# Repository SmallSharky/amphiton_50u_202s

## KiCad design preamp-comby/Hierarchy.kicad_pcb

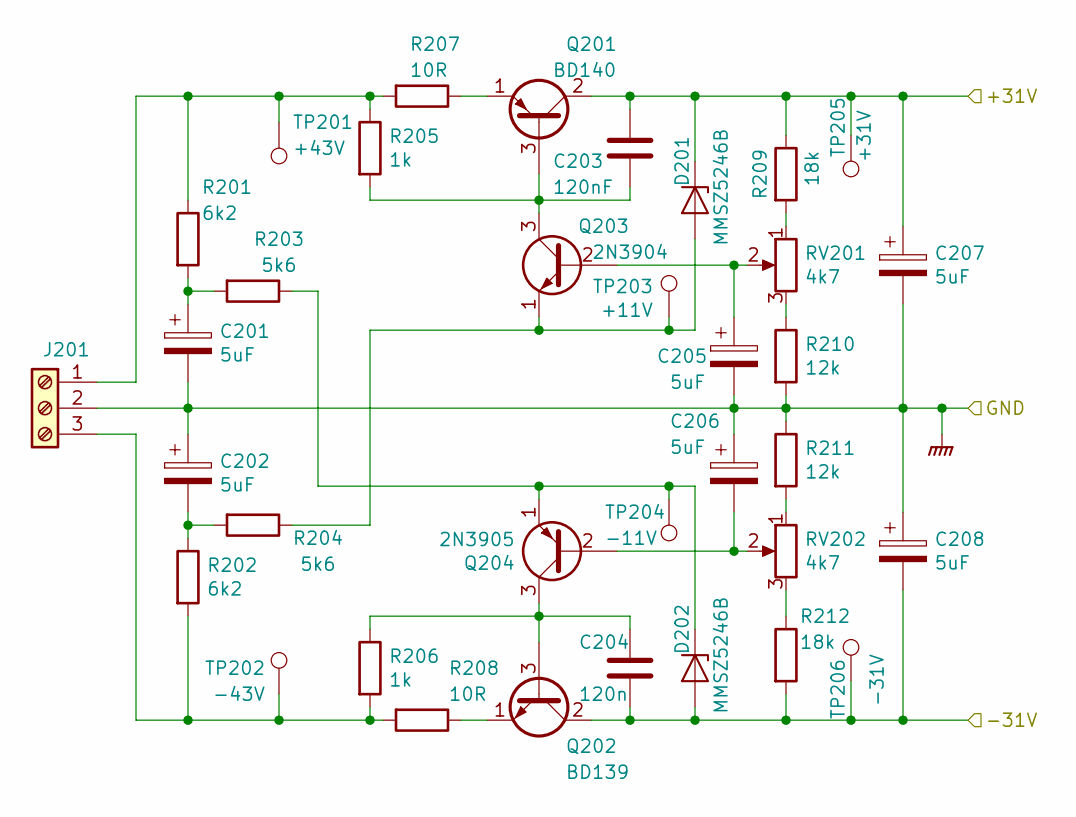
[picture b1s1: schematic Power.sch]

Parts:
C201, C202, C205, C206, C207, C208: 5uF; CP_Radial_D5.0mm_P2.00mm
C203: 120nF; C_Rect_L7.2mm_W3.0mm_P5.00mm_FKS2_FKP2_MKS2_MKP2
C204: 120n; C_Rect_L7.2mm_W3.0mm_P5.00mm_FKS2_FKP2_MKS2_MKP2
D201, D202: MMSZ5246B; D_SOD-123
J201: Screw_Terminal_01x03; TerminalBlock_MetzConnect_Type086_RT03403HBLC_1x03_P3.81mm_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
Q201: BD140; TO-126-3_Vertical
Q202: BD139; TO-126-3_Vertical
Q203: 2N3904; TO-92_Inline
Q204: 2N3905; TO-92_Inline
R201, R202: 6k2; R_1206_3216Metric_Pad1.42x1.75mm_HandSolder
R203, R204: 5k6; R_1206_3216Metric_Pad1.42x1.75mm_HandSolder
R205, R206: 1k; R_1206_3216Metric_Pad1.42x1.75mm_HandSolder
R207, R208: 10R; R_1206_3216Metric_Pad1.42x1.75mm_HandSolder
R209, R212: 18k; R_1206_3216Metric_Pad1.42x1.75mm_HandSolder
R210, R211: 12k; R_1206_3216Metric_Pad1.42x1.75mm_HandSolder
RV201, RV202: 4k7; Potentiometer_Bourns_3296W_Vertical
TP201: +43V; TestPoint_Pad_D1.5mm
TP202: -43V; TestPoint_Pad_D1.5mm
TP203: +11V; TestPoint_Pad_D1.5mm
TP204: -11V; TestPoint_Pad_D1.5mm
TP205: +31V; TestPoint_Pad_D1.5mm
TP206: -31V; TestPoint_Pad_D1.5mm

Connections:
/Power/+31V: C203.1, C207.1, D201.1 (K), Q201.2 (C), R209.1, TP205.1; also elsewhere on the board
/Power/-31V: C204.2, C208.2, D202.2 (A), Q202.2 (C), R212.2, TP206.1; also elsewhere on the board
GNDA: C201.2, C202.1, C205.2, C206.1, C207.2, C208.1, J201.2, R210.2, R211.1; also elsewhere on the board
unnamed: C201.1, R201.2, R203.2
unnamed: C202.2, R202.1, R204.2
unnamed: C203.2, Q201.3 (B), Q203.3 (C), R205.2
unnamed: C204.1, Q202.3 (B), Q204.3 (C), R206.1
unnamed: C205.1, Q203.2 (B), RV201.2
unnamed: C206.2, Q204.2 (B), RV202.2
unnamed: D201.2 (A), Q203.1 (E), R204.1, TP203.1
unnamed: D202.1 (K), Q204.1 (E), R203.1, TP204.1
unnamed: J201.1, R201.1, R205.1, R207.2, TP201.1
unnamed: J201.3, R202.2, R206.2, R208.2, TP202.1
unnamed: Q201.1 (E), R207.1
unnamed: Q202.1 (E), R208.1
unnamed: R209.2, RV201.1
unnamed: R210.1, RV201.3
unnamed: R211.2, RV202.1
unnamed: R212.1, RV202.3

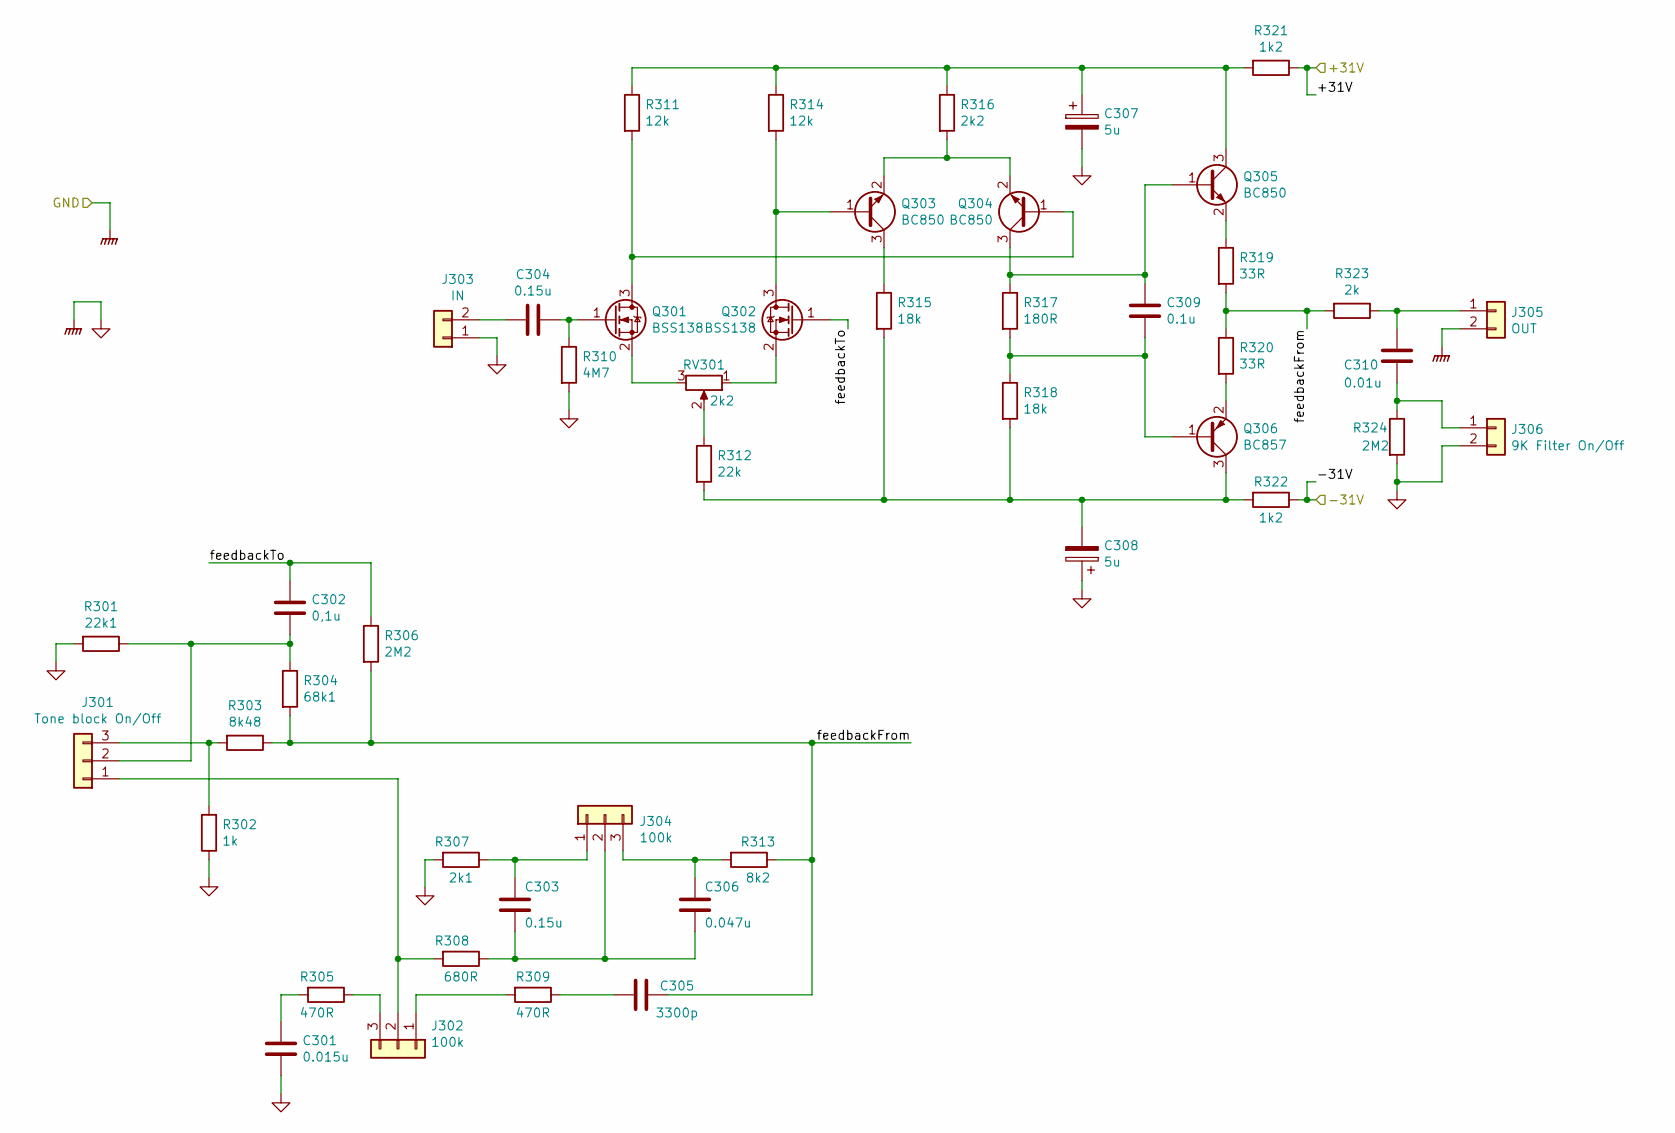
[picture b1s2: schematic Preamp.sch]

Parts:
C301: 0.015u; C_Rect_L7.2mm_W3.0mm_P5.00mm_FKS2_FKP2_MKS2_MKP2
C302: 0,1u; C_Rect_L7.2mm_W3.0mm_P5.00mm_FKS2_FKP2_MKS2_MKP2
C303, C304: 0.15u; C_Rect_L7.2mm_W3.0mm_P5.00mm_FKS2_FKP2_MKS2_MKP2
C305: 3300p; C_Rect_L7.2mm_W3.0mm_P5.00mm_FKS2_FKP2_MKS2_MKP2
C306: 0.047u; C_Rect_L7.2mm_W3.0mm_P5.00mm_FKS2_FKP2_MKS2_MKP2
C307, C308: 5u; CP_Radial_D5.0mm_P2.00mm
C309: 0.1u; C_Rect_L7.2mm_W3.0mm_P5.00mm_FKS2_FKP2_MKS2_MKP2
C310: 0.01u; C_Rect_L7.2mm_W3.0mm_P5.00mm_FKS2_FKP2_MKS2_MKP2
J301: Tone block On/Off; PinHeader_1x03_P2.54mm_Vertical
J302, J304: 100k; PinHeader_1x03_P2.54mm_Vertical
J303: IN; PinHeader_1x02_P2.54mm_Vertical
J305: OUT; PinHeader_1x02_P2.54mm_Vertical
J306: 9K Filter On/Off; PinHeader_1x02_P2.54mm_Vertical
Q301, Q302: BSS138; SOT-23
Q303, Q304, Q305: BC850; SOT-23
Q306: BC857; SOT-23
R301: 22k1; R_1206_3216Metric_Pad1.42x1.75mm_HandSolder
R302: 1k; R_1206_3216Metric_Pad1.42x1.75mm_HandSolder
R303: 8k48; R_1206_3216Metric_Pad1.42x1.75mm_HandSolder
R304: 68k1; R_1206_3216Metric_Pad1.42x1.75mm_HandSolder
R305, R309: 470R; R_1206_3216Metric_Pad1.42x1.75mm_HandSolder
R306, R324: 2M2; R_1206_3216Metric_Pad1.42x1.75mm_HandSolder
R307: 2k1; R_1206_3216Metric_Pad1.42x1.75mm_HandSolder
R308: 680R; R_1206_3216Metric_Pad1.42x1.75mm_HandSolder
R310: 4M7; R_1206_3216Metric_Pad1.42x1.75mm_HandSolder
R311, R314: 12k; R_1206_3216Metric_Pad1.42x1.75mm_HandSolder
R312: 22k; R_1206_3216Metric_Pad1.42x1.75mm_HandSolder
R313: 8k2; R_1206_3216Metric_Pad1.42x1.75mm_HandSolder
R315, R318: 18k; R_1206_3216Metric_Pad1.42x1.75mm_HandSolder
R316: 2k2; R_1206_3216Metric_Pad1.42x1.75mm_HandSolder
R317: 180R; R_1206_3216Metric_Pad1.42x1.75mm_HandSolder
R319, R320: 33R; R_1206_3216Metric_Pad1.42x1.75mm_HandSolder
R321, R322: 1k2; R_1206_3216Metric_Pad1.42x1.75mm_HandSolder
R323: 2k; R_1206_3216Metric_Pad1.42x1.75mm_HandSolder
RV301: 2k2; Potentiometer_Bourns_3296W_Vertical

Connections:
/Power/+31V: R321.1; also elsewhere on the board
/Power/-31V: R322.1; also elsewhere on the board
/Preamp/feedbackFrom: C305.1, R303.1, R304.2, R306.2, R313.1, R319.2, R320.1, R323.2
/Preamp/feedbackTo: C302.1, Q302.1 (G), R306.1
GNDA: C301.2, C307.2, C308.1, J303.1, J305.2, J306.2, R301.2, R302.1, R307.2, R310.2, R324.2; also elsewhere on the board
unnamed: C301.1, R305.2
unnamed: C302.2, J301.2, R301.1, R304.1
unnamed: C303.1, J304.1, R307.1
unnamed: C303.2, C306.2, J304.2, R308.1
unnamed: C304.1, Q301.1 (G), R310.1
unnamed: C304.2, J303.2
unnamed: C305.2, R309.1
unnamed: C306.1, J304.3, R313.2
unnamed: C307.1, Q305.3 (C), R311.1, R314.1, R316.1, R321.2
unnamed: C308.2, Q306.3 (C), R312.2, R315.2, R318.2, R322.2
unnamed: C309.1, Q304.3 (C), Q305.1 (B), R317.1
unnamed: C309.2, Q306.1 (B), R317.2, R318.1
unnamed: C310.1, J306.1, R324.1
unnamed: C310.2, J305.1, R323.1
unnamed: J301.1, J302.2, R308.2
unnamed: J301.3, R302.2, R303.2
unnamed: J302.1, R309.2
unnamed: J302.3, R305.1
unnamed: Q301.2 (S), RV301.3
unnamed: Q301.3 (D), Q304.1 (B), R311.2
unnamed: Q302.2 (S), RV301.1
unnamed: Q302.3 (D), Q303.1 (B), R314.2
unnamed: Q303.2 (E), Q304.2 (E), R316.2
unnamed: Q303.3 (C), R315.1
unnamed: Q305.2 (E), R319.1
unnamed: Q306.2 (E), R320.2
unnamed: R312.1, RV301.2

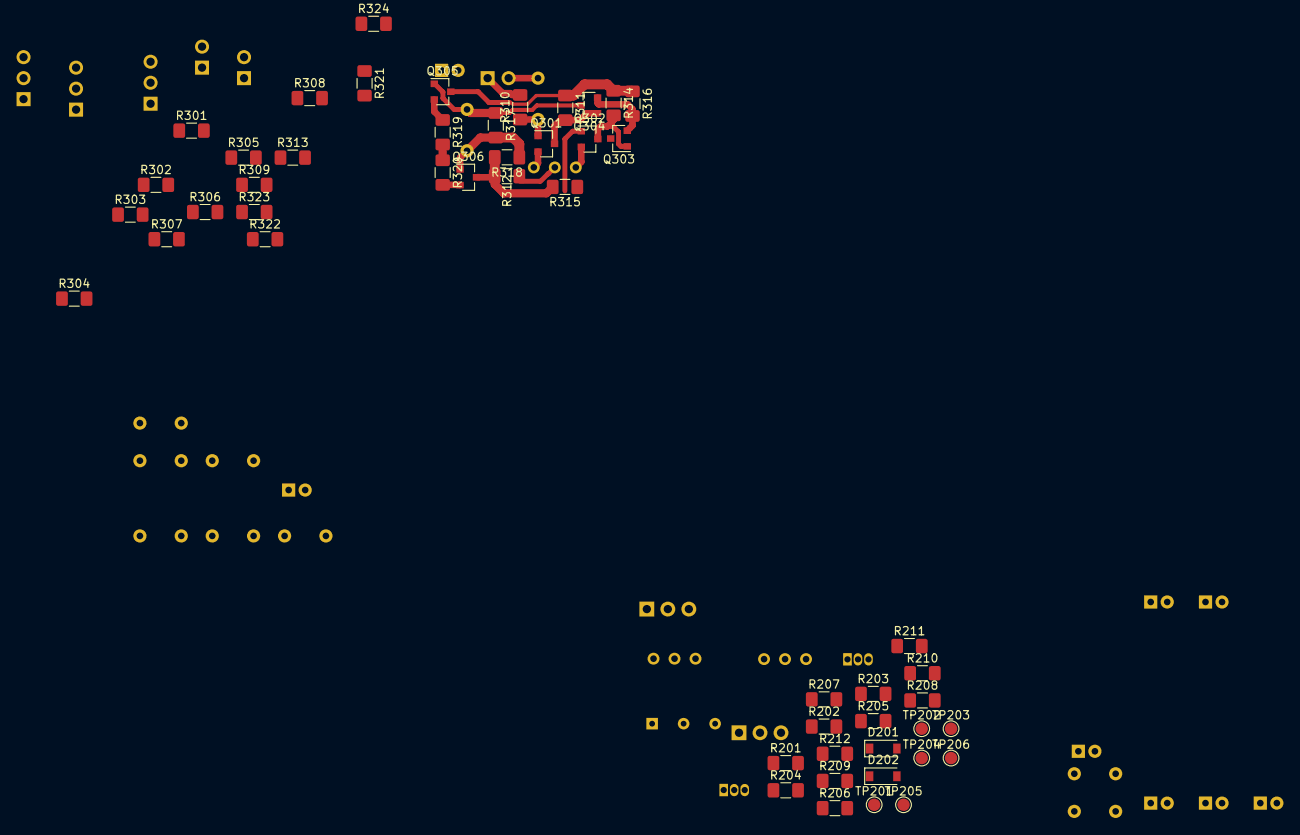
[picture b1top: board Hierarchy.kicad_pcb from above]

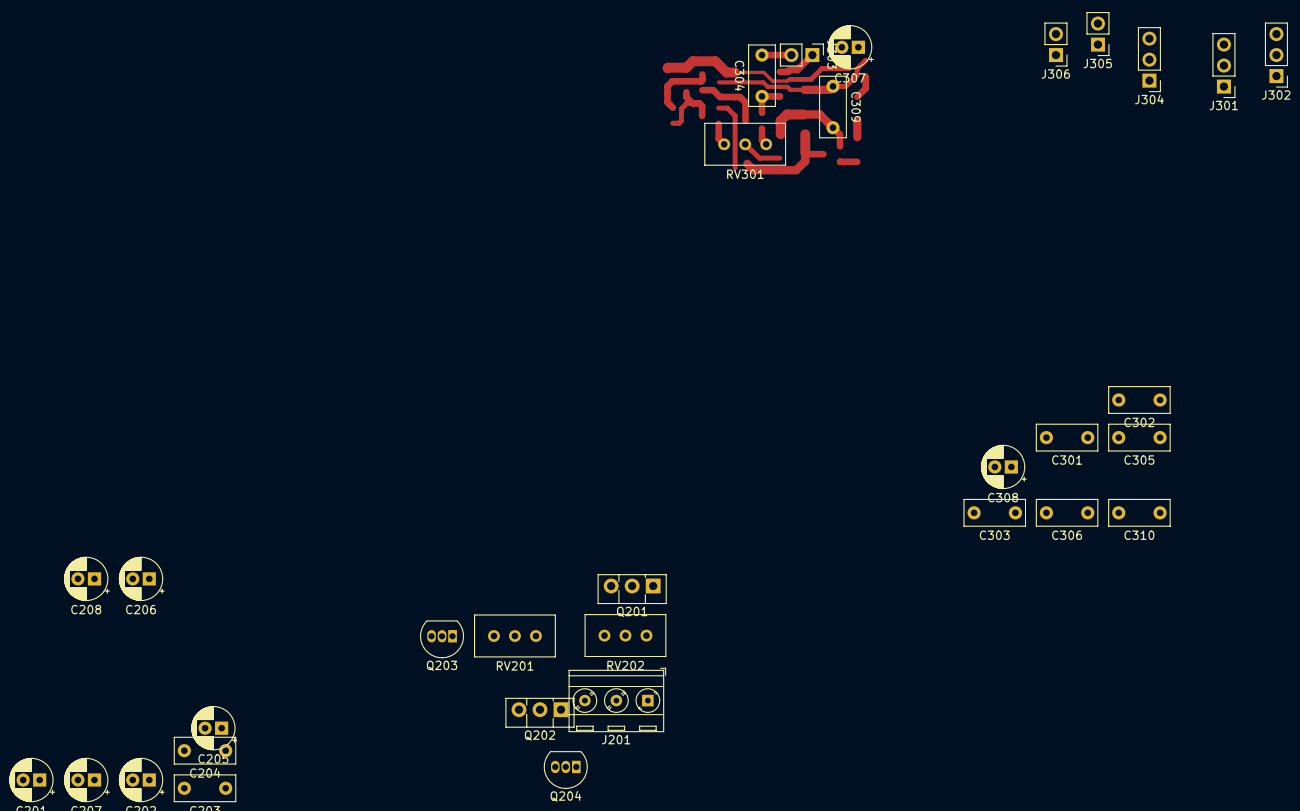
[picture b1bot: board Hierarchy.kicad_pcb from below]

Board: 2 copper layers, 82 parts (32 on the bottom side), 48 nets.

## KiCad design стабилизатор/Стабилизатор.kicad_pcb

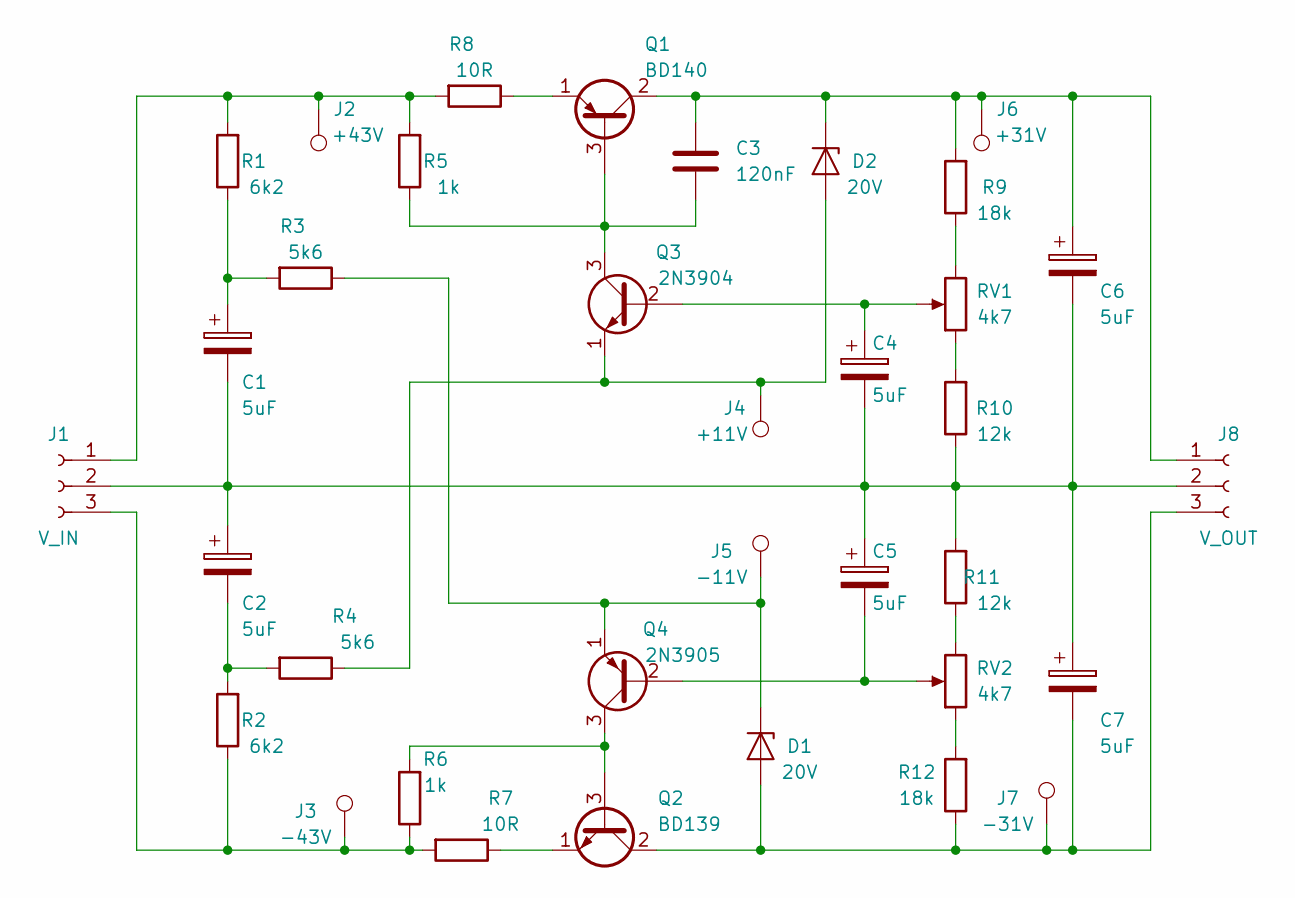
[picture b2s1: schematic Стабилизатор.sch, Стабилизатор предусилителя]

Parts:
C1, C2, C4, C5, C6, C7: 5uF; CP_Radial_D5.0mm_P2.50mm
C3: 120nF; C_0805_HandSoldering
D1, D2: 20V; D_DO-35_SOD27_P7.62mm_Horizontal
J1: V_IN; Pin_Header_Straight_1x03_Pitch2.54mm
J2: +43V; Measurement_Point_Round-SMD-Pad_Small
J3: -43V; Measurement_Point_Round-SMD-Pad_Small
J4: +11V; Measurement_Point_Round-SMD-Pad_Small
J5: -11V; Measurement_Point_Round-SMD-Pad_Small
J6: +31V; Measurement_Point_Round-SMD-Pad_Small
J7: -31V; Measurement_Point_Round-SMD-Pad_Small
J8: V_OUT; Pin_Header_Straight_1x03_Pitch2.54mm
Q1: BD140; TO-126_Vertical
Q2: BD139; TO-126_Vertical
Q3: 2N3904; TO-92_Molded_Wide
Q4: 2N3905; TO-92_Molded_Wide
R1, R2: 6k2; R_1206_HandSoldering
R3, R4: 5k6; R_1206_HandSoldering
R5, R6: 1k; R_1206_HandSoldering
R7, R8: 10R; R_1206_HandSoldering
R9, R12: 18k; R_1206_HandSoldering
R10, R11: 12k; R_1206_HandSoldering
RV1, RV2: 4k7; Potentiometer_Trimmer_Bourns_3266Y

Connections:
unnamed: C1.1, R1.1, R3.2
unnamed: C1.2, C2.1, C4.2, C5.1, C6.2, C7.1, J1.2, J8.2, R10.1, R11.2
unnamed: C2.2, R2.2, R4.2
unnamed: C3.1, C6.1, D2.1 (K), J6.1, J8.1, Q1.2 (C), R9.2
unnamed: C3.2, Q1.3 (B), Q3.3 (C), R5.1
unnamed: C4.1, Q3.2 (B), RV1.2
unnamed: C5.2, Q4.2 (B), RV2.2
unnamed 7: C7.2, D1.2 (A), J7.1, J8.3, Q2.2 (C), R12.1; also elsewhere on the board
unnamed 8: Q2.3 (B), Q4.3 (C), R6.2; also elsewhere on the board
unnamed: D1.1 (K), J5.1, Q4.1 (E), R3.1
unnamed: D2.2 (A), J4.1, Q3.1 (E), R4.1
unnamed: J1.1, J2.1, R1.2, R5.2, R8.2
unnamed: J1.3, J3.1, R2.1, R6.1, R7.2
unnamed: Q1.1 (E), R8.1
unnamed: Q2.1 (E), R7.1
unnamed: R9.1, RV1.3
unnamed: R10.2, RV1.1
unnamed: R11.1, RV2.3
unnamed: R12.2, RV2.1

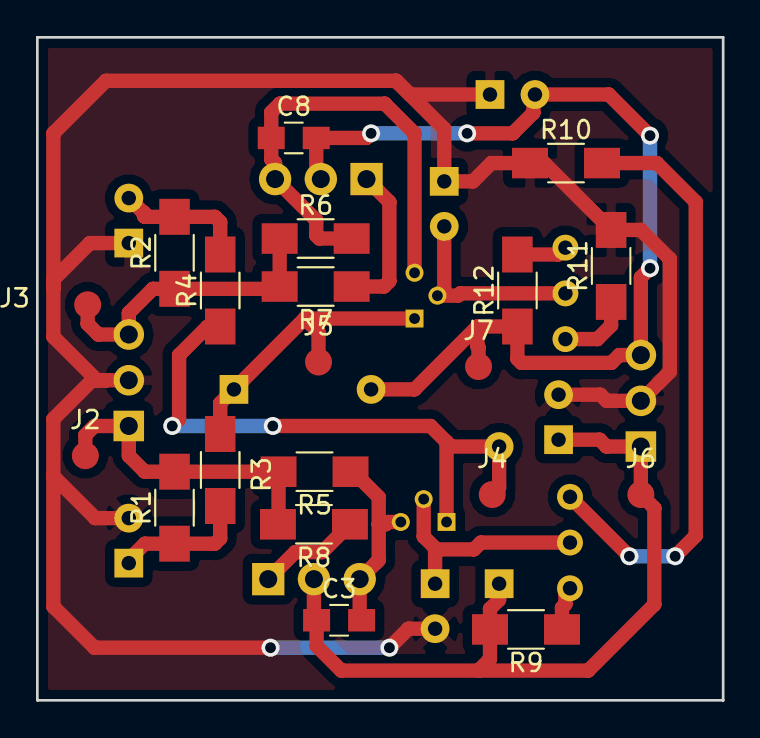
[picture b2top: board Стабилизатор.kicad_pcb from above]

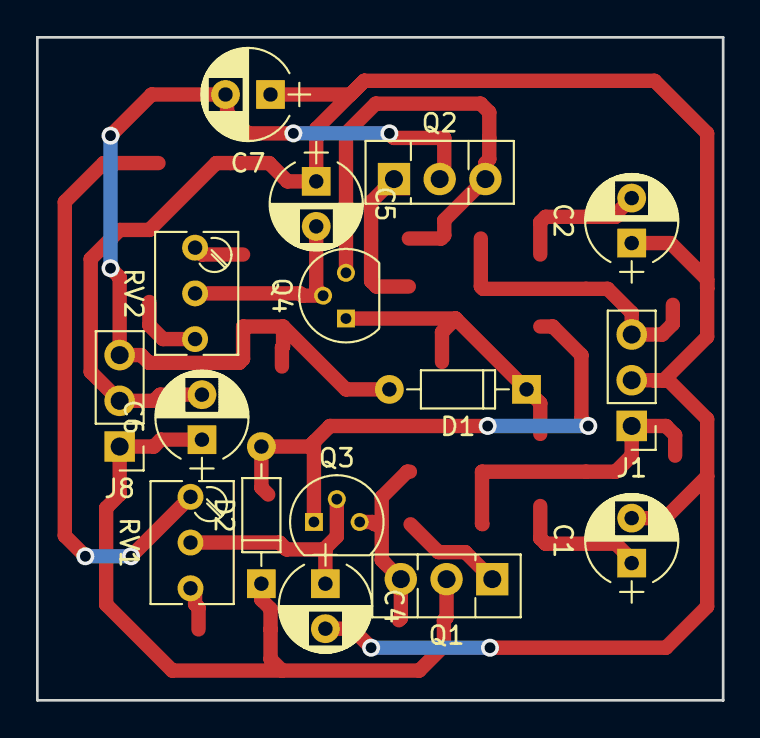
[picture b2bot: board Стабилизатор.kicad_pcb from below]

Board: 2 copper layers, 38.1 x 36.8 mm, 36 parts (16 on the bottom side), 19 nets.

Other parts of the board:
C8: 120nF; C_0805_HandSoldering

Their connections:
unnamed 7: C8.2; also elsewhere on the board
unnamed 8: C8.1; also elsewhere on the board

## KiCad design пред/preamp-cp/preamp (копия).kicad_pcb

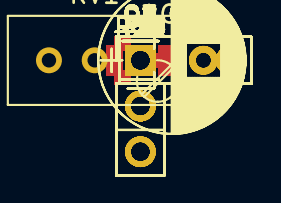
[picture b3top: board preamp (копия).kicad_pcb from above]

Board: 2 copper layers, 48 parts (0 on the bottom side), 32 nets, no tracks yet.

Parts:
C1, C2, C3, C4, C5, C6, C7, C10: C; C_Rect_L7.2mm_W2.5mm_P5.00mm_FKS2_FKP2_MKS2_MKP2
C8, C9: C; CP_Radial_D8.0mm_P3.50mm
P1, P5, P6: CONN_01X02; Pin_Header_Straight_1x02_Pitch2.54mm
P2, P3, P4, P7: CONN_01X03; Pin_Header_Straight_1x03_Pitch2.54mm
Q1, Q2: BSS138; SOT-23
Q3, Q4, Q6: BC857; SOT-23
Q5: BC850; SOT-23
R1, R2, R3, R4, R5, R6, R7, R8, R9, R10, R11, R12, R13, R14, R15, R16, R17, R18, R19, R20, R21, R22, R23, R24: R; R_1206
RV1: POT; Potentiometer_Trimmer_Bourns_3296W

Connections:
GNDREF: C3.2, C8.1, C9.1, P1.2, P5.2, P6.2, P7.2, R1.2, R4.2, R7.2, R14.2, R22.2
unnamed: C1.1, Q1.1, R1.1
unnamed: C1.2, P1.1
unnamed: C2.1, P2.2, R7.1, R8.1
unnamed: C2.2, Q2.1, R9.1
unnamed: C3.1, R11.2
unnamed: C4.1, C6.1, P4.2, R13.1
unnamed: C4.2, P4.3, R14.1
unnamed: C5.1, Q6.1, R15.2, R16.1
unnamed: C5.2, Q4.3, Q5.1, R15.1
unnamed: C6.2, P4.1, R20.2
unnamed: C7.1, R3.1, R8.2, R9.2, R18.1, R19.2, R20.1, R21.1
unnamed: C7.2, R17.1
unnamed: C8.2, Q5.3, R2.1, R6.1, R12.1, R23.2
unnamed: C9.2, Q6.3, R5.2, R10.2, R16.2, R24.2
unnamed: C10.1, P5.1, R22.1
unnamed: C10.2, P6.1, R21.2
unnamed: P2.1, P3.2, R13.2
unnamed: P2.3, R3.2, R4.1
unnamed: P3.1, R17.2
unnamed: P3.3, R11.1
unnamed: P7.1, R23.1
unnamed: P7.3, R24.1
unnamed: Q1.2, RV1.3
unnamed: Q1.3, Q4.1, R2.2
unnamed: Q2.2, RV1.1
unnamed: Q2.3, Q3.1, R6.2
unnamed: Q3.2, Q4.2, R12.2
unnamed: Q3.3, R10.1
unnamed: Q5.2, R18.2
unnamed: Q6.2, R19.1
unnamed: R5.1, RV1.2

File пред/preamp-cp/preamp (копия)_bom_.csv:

Component,Description,Part,References,Value,Footprint,Quantity Per PCB,Datasheet
1,b'Unpolarized capacitor',b'C',b'C3',b'0.015u',b'C_Rect_L7.2mm_W2.5mm_P5.00mm_FKS2_FKP2_MKS2_MKP2',b'1',b''
2,b'Unpolarized capacitor',b'C',b'C10',b'0.01u',b'C_Rect_L7.2mm_W2.5mm_P5.00mm_FKS2_FKP2_MKS2_MKP2',b'1',b''
3,b'Unpolarized capacitor',b'C',b'C6',b'0.047u',b'C_Rect_L7.2mm_W2.5mm_P5.00mm_FKS2_FKP2_MKS2_MKP2',b'1',b''
4,b'Unpolarized capacitor',b'C',b'C1 C4',b'0.15u',b'C_Rect_L7.2mm_W2.5mm_P5.00mm_FKS2_FKP2_MKS2_MKP2',b'2',b''
5,b'Unpolarized capacitor',b'C',b'C2 C5',b'0.1u',b'C_Rect_L7.2mm_W2.5mm_P5.00mm_FKS2_FKP2_MKS2_MKP2',b'2',b''
6,b'Unpolarized capacitor',b'C',b'C7',b'3300p',b'C_Rect_L7.2mm_W2.5mm_P5.00mm_FKS2_FKP2_MKS2_MKP2',b'1',b''
7,b'Unpolarized capacitor',b'C',b'C8 C9',b'5u',b'CP_Radial_D8.0mm_P3.50mm',b'2',b''
8,"b'Generic connector, single row, 01x02'",b'Conn_01x02',b'P1 P5 P6',b'CONN_01X02',b'Pin_Header_Straight_1x02_Pitch2.54mm',b'3',b''
9,"b'Generic connector, single row, 01x03'",b'Conn_01x03',b'P2 P7',b'CONN_01X03',b'Pin_Header_Straight_1x03_Pitch2.54mm',b'2',b''
10,"b'45V Vce, 0.8A Ic, NPN, SOT-23'",b'BC850',b'Q5',b'BC850',b'SOT-23',b'1',b'http://www.fairchildsemi.com/ds/BC/BC817.pdf'
11,"b'45V Vce, 0.8A Ic, PNP, SOT-23'",b'BC857',b'Q3 Q4 Q6',b'BC857',b'SOT-23',b'3',b'http://www.fairchildsemi.com/ds/BC/BC807.pdf'
12,"b'50V Vds, 0.22 A Id, N-channel MOSFET, SOT-23'",b'BSS138',b'Q1 Q2',b'BSS138',b'SOT-23',b'2',b'https://www.fairchildsemi.com/datasheets/BS/BSS138.pdf'
13,"b'Generic connector, single row, 01x03'",b'Conn_01x03',b'R25 R26',b'100k',b'Pin_Header_Straight_1x03_Pitch2.54mm',b'2',b''
14,b'Resistor',b'R',b'R2 R6',b'12k',b'R_1206',b'2',b''
15,b'Resistor',b'R',b'R15',b'180R',b'R_1206',b'1',b''
16,b'Resistor',b'R',b'R10 R16',b'18k',b'R_1206',b'2',b''
17,b'Resistor',b'R',b'R4',b'1k',b'R_1206',b'1',b''
18,b'Resistor',b'R',b'R23 R24',b'1k2',b'R_1206',b'2',b''
19,b'Resistor',b'R',b'R9 R22',b'2.2M',b'R_1206',b'2',b''
20,b'Resistor',b'R',b'R7',b'22.1k',b'R_1206',b'1',b''
21,b'Resistor',b'R',b'R5',b'22k',b'R_1206',b'1',b''
22,b'Resistor',b'R',b'R21',b'2k',b'R_1206',b'1',b''
23,b'Resistor',b'R',b'R14',b'2k1',b'R_1206',b'1',b''
24,b'Resistor',b'R',b'R12',b'2k2',b'R_1206',b'1',b''
25,b'Resistor',b'R',b'R18 R19',b'33R',b'R_1206',b'2',b''
26,b'Resistor',b'R',b'R1',b'4.7M',b'R_1206',b'1',b''
27,b'Resistor',b'R',b'R11 R17',b'470R',b'R_1206',b'2',b''
28,b'Resistor',b'R',b'R8',b'68.1k',b'R_1206',b'1',b''
29,b'Resistor',b'R',b'R13',b'680R',b'R_1206',b'1',b''
30,b'Resistor',b'R',b'R3',b'8.48k',b'R_1206',b'1',b''
31,b'Resistor',b'R',b'R20',b'8k2',b'R_1206',b'1',b''
32,b'Potentiometer',b'POT',b'RV1',b'2k2',b'Potentiometer_Trimmer_Bourns_3296W',b'1',b''





Component Groups:,32
Component Count:,48
Fitted Components:,48
Number of PCBs:,1
Total components:,48
Schematic Version:,
Schematic Date:,
BoM Date:,b' 11  2018 03:27:35'
Schematic Source:,b'/backup/git/amphiton_50u_202s//preamp ().sch'
KiCad Version:,b'Eeschema 4.0.7'

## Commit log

2017-08-22 Created
2017-08-22 Создана печатная плата, назначены посадочные места
2017-08-27 Начата трассировка
2018-03-14 add new board for preamp
2018-03-14 Переделана печатная плата преда
2018-05-08 Добавлена схема стабилизатора предусилителя
2018-05-10 Привязка корпусов
2018-05-10 Разводка платы стабилизатора
2019-09-30 Remove old projects
2019-09-30 Add comby preamp project
2019-10-01 Draw schematic of comby
2019-10-01 Draw multisheet schematic for comby
2019-10-01 Finish schematic, start routing
2019-10-01 Remove trash
2019-10-03 Routing in progress
